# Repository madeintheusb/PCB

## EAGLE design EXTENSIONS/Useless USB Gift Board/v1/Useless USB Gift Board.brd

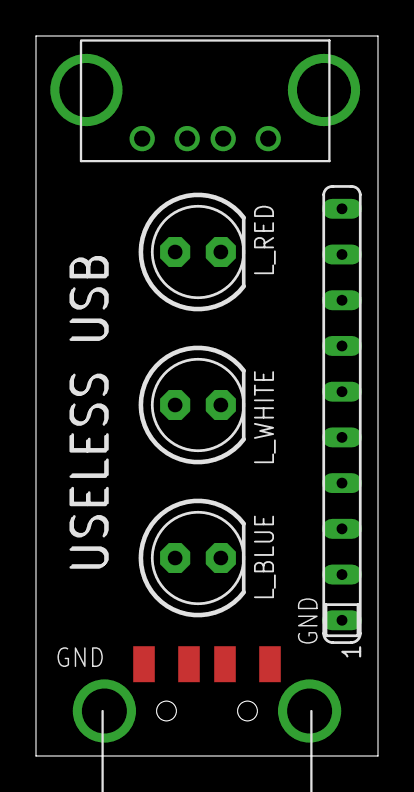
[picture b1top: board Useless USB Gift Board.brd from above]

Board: 2 copper layers, 19.0 x 40.0 mm, 6 parts (0 on the bottom side), 7 nets, no tracks yet.

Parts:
L_BLUE: LED5MM
L_RED: LED5MM
L_WHITE: LED5MM
RN1: SIP10
U$1: USB; USB-FEMALE-A-PTH
X1: USB-A; MOLEX_480371000

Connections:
unnamed: RN1.1, U$1.GND, X1.4
unnamed: L_BLUE.K, RN1.2
unnamed: U$1.D+, X1.3
unnamed: U$1.D-, X1.2
unnamed: L_RED.K, RN1.8
unnamed: L_WHITE.K, RN1.6
VCC: L_BLUE.A, L_RED.A, L_WHITE.A, U$1.VBUS, X1.1

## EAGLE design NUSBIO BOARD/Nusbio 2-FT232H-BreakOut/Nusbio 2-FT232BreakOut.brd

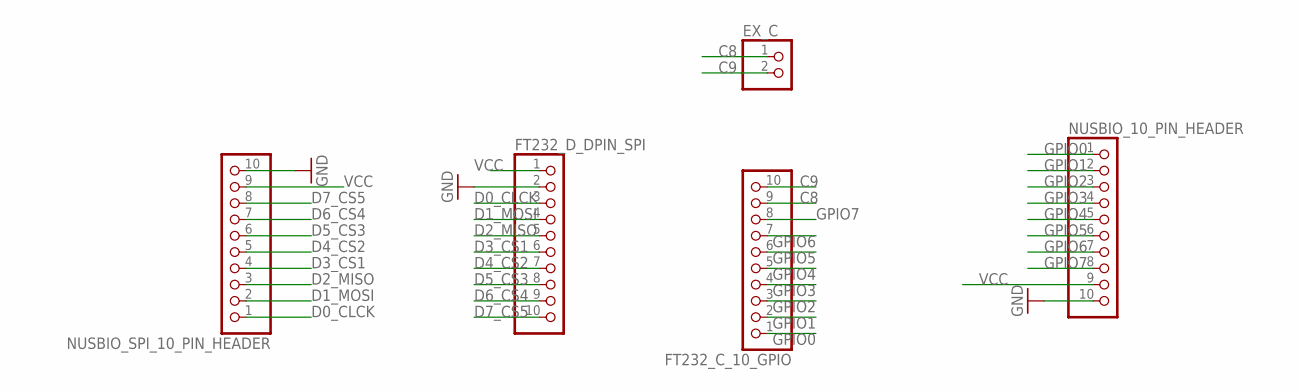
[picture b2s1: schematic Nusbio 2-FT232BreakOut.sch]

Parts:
EX_C: PINHD-1X2; 1X02
FT232_C_10_GPIO, FT232_D_DPIN_SPI: PINHD-1X10; 1X10
NUSBIO_10_PIN_HEADER: PINHD-1X10; 1X10
NUSBIO_SPI_10_PIN_HEADER: PINHD-1X10; 1X10

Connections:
C8: EX_C.1, FT232_C_10_GPIO.9
C9: EX_C.2, FT232_C_10_GPIO.10
D0_CLCK: FT232_D_DPIN_SPI.3, NUSBIO_SPI_10_PIN_HEADER.1
D1_MOSI: FT232_D_DPIN_SPI.4, NUSBIO_SPI_10_PIN_HEADER.2
D2_MISO: FT232_D_DPIN_SPI.5, NUSBIO_SPI_10_PIN_HEADER.3
D3_CS1: FT232_D_DPIN_SPI.6, NUSBIO_SPI_10_PIN_HEADER.4
D4_CS2: FT232_D_DPIN_SPI.7, NUSBIO_SPI_10_PIN_HEADER.5
D5_CS3: FT232_D_DPIN_SPI.8, NUSBIO_SPI_10_PIN_HEADER.6
D6_CS4: FT232_D_DPIN_SPI.9, NUSBIO_SPI_10_PIN_HEADER.7
D7_CS5: FT232_D_DPIN_SPI.10, NUSBIO_SPI_10_PIN_HEADER.8
GND: FT232_D_DPIN_SPI.2, NUSBIO_10_PIN_HEADER.10, NUSBIO_SPI_10_PIN_HEADER.10
GPIO0: FT232_C_10_GPIO.1, NUSBIO_10_PIN_HEADER.1
GPIO1: FT232_C_10_GPIO.2, NUSBIO_10_PIN_HEADER.2
GPIO2: FT232_C_10_GPIO.3, NUSBIO_10_PIN_HEADER.3
GPIO3: FT232_C_10_GPIO.4, NUSBIO_10_PIN_HEADER.4
GPIO4: FT232_C_10_GPIO.5, NUSBIO_10_PIN_HEADER.5
GPIO5: FT232_C_10_GPIO.6, NUSBIO_10_PIN_HEADER.6
GPIO6: FT232_C_10_GPIO.7, NUSBIO_10_PIN_HEADER.7
GPIO7: FT232_C_10_GPIO.8, NUSBIO_10_PIN_HEADER.8
VCC: FT232_D_DPIN_SPI.1, NUSBIO_10_PIN_HEADER.9, NUSBIO_SPI_10_PIN_HEADER.9

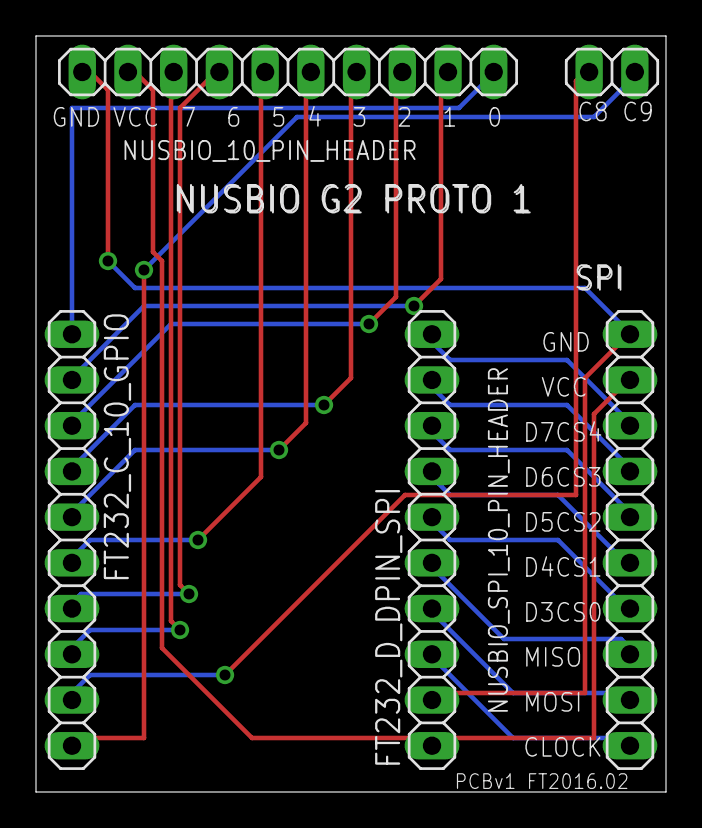
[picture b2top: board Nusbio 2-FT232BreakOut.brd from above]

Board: 2 copper layers, 35.0 x 42.0 mm, 5 parts (0 on the bottom side), 20 nets.

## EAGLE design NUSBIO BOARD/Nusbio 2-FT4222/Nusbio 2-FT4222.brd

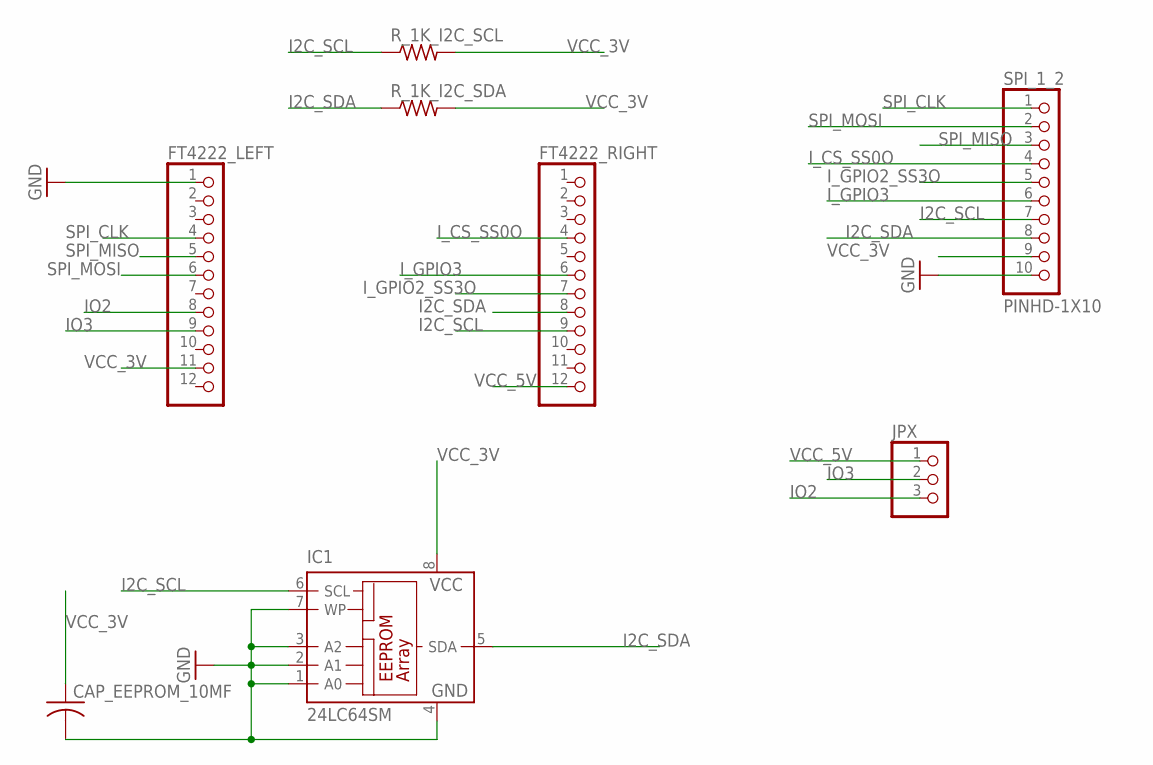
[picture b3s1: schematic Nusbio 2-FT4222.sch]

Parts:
CAP_EEPROM_10MF: C-USC1206; C1206
FT4222_LEFT, FT4222_RIGHT: PINHD-1X12; 1X12
IC1: 24LC64SM; SO-08M
JPX: PINHD-1X3; 1X03
R_1K_I2C_SCL, R_1K_I2C_SDA: R-US_R1206; R1206
SPI_1_2: PINHD-1X10; 1X10-BIG

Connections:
GND: CAP_EEPROM_10MF.2, FT4222_LEFT.1, IC1.1 (A0), IC1.2 (A1), IC1.3 (A2), IC1.4 (GND), IC1.7 (WP), SPI_1_2.10
I2C_SCL: FT4222_RIGHT.9, IC1.6 (SCL), R_1K_I2C_SCL.1, SPI_1_2.7
I2C_SDA: FT4222_RIGHT.8, IC1.5 (SDA), R_1K_I2C_SDA.1, SPI_1_2.8
IO2: FT4222_LEFT.8, JPX.3
IO3: FT4222_LEFT.9, JPX.2
I_CS_SS0O: FT4222_RIGHT.4, SPI_1_2.4
I_GPIO2_SS3O: FT4222_RIGHT.7, SPI_1_2.5
I_GPIO3: FT4222_RIGHT.6, SPI_1_2.6
SPI_CLK: FT4222_LEFT.4, SPI_1_2.1
SPI_MISO: FT4222_LEFT.5, SPI_1_2.3
SPI_MOSI: FT4222_LEFT.6, SPI_1_2.2
VCC_3V: CAP_EEPROM_10MF.1, FT4222_LEFT.11, IC1.8 (VCC), R_1K_I2C_SCL.2, R_1K_I2C_SDA.2, SPI_1_2.9
VCC_5V: FT4222_RIGHT.12, JPX.1

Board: 2 copper layers, 8 parts (4 on the bottom side), 13 nets, no tracks yet.

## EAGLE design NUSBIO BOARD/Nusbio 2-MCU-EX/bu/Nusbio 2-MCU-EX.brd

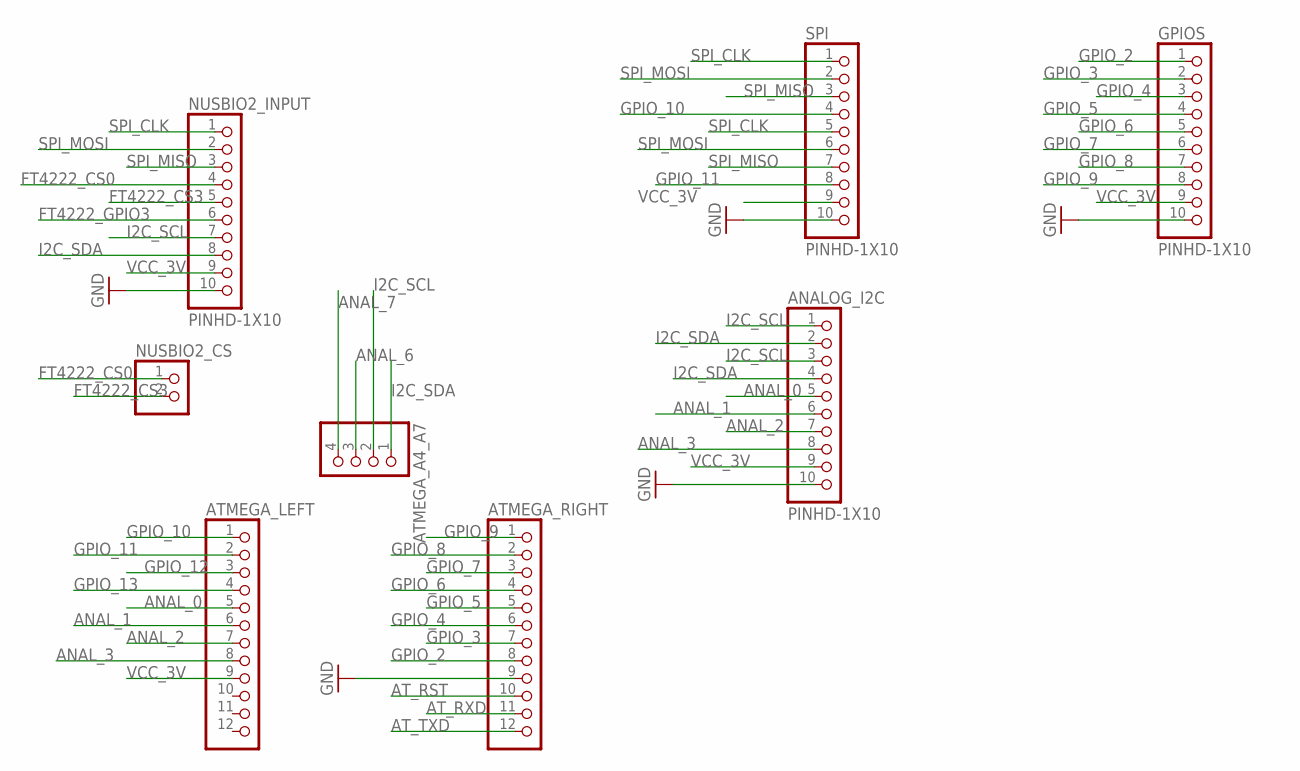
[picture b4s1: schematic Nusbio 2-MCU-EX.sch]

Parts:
ANALOG_I2C: PINHD-1X10; 1X10-BIG
ATMEGA_A4_A7: PINHD-1X4; 1X04
ATMEGA_LEFT: PINHD-1X12; 1X12
ATMEGA_RIGHT: PINHD-1X12; 1X12
GPIOS: PINHD-1X10; 1X10-BIG
NUSBIO2_CS: PINHD-1X2; 1X02
NUSBIO2_INPUT: PINHD-1X10; 1X10-BIG
SPI: PINHD-1X10; 1X10-BIG

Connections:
ANAL_0: ANALOG_I2C.5, ATMEGA_LEFT.5
ANAL_1: ANALOG_I2C.6, ATMEGA_LEFT.6
ANAL_2: ANALOG_I2C.7, ATMEGA_LEFT.7
ANAL_3: ANALOG_I2C.8, ATMEGA_LEFT.8
ANAL_6: ATMEGA_A4_A7.3
ANAL_7: ATMEGA_A4_A7.4
AT_RST: ATMEGA_RIGHT.10
AT_RXD: ATMEGA_RIGHT.11
AT_TXD: ATMEGA_RIGHT.12
FT4222_CS0: NUSBIO2_CS.1, NUSBIO2_INPUT.4
FT4222_CS3: NUSBIO2_CS.2, NUSBIO2_INPUT.5
FT4222_GPIO3: NUSBIO2_INPUT.6
GND: ANALOG_I2C.10, ATMEGA_RIGHT.9, GPIOS.10, NUSBIO2_INPUT.10, SPI.10
GPIO_2: ATMEGA_RIGHT.8, GPIOS.1
GPIO_3: ATMEGA_RIGHT.7, GPIOS.2
GPIO_4: ATMEGA_RIGHT.6, GPIOS.3
GPIO_5: ATMEGA_RIGHT.5, GPIOS.4
GPIO_6: ATMEGA_RIGHT.4, GPIOS.5
GPIO_7: ATMEGA_RIGHT.3, GPIOS.6
GPIO_8: ATMEGA_RIGHT.2, GPIOS.7
GPIO_9: ATMEGA_RIGHT.1, GPIOS.8
GPIO_10: ATMEGA_LEFT.1, SPI.4
GPIO_11: ATMEGA_LEFT.2, SPI.8
GPIO_12: ATMEGA_LEFT.3
GPIO_13: ATMEGA_LEFT.4
I2C_SCL: ANALOG_I2C.1, ANALOG_I2C.3, ATMEGA_A4_A7.2, NUSBIO2_INPUT.7
I2C_SDA: ANALOG_I2C.2, ANALOG_I2C.4, ATMEGA_A4_A7.1, NUSBIO2_INPUT.8
SPI_CLK: NUSBIO2_INPUT.1, SPI.1, SPI.5
SPI_MISO: NUSBIO2_INPUT.3, SPI.3, SPI.7
SPI_MOSI: NUSBIO2_INPUT.2, SPI.2, SPI.6
VCC_3V: ANALOG_I2C.9, ATMEGA_LEFT.9, GPIOS.9, NUSBIO2_INPUT.9, SPI.9

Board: 2 copper layers, 8 parts (0 on the bottom side), 23 nets, no tracks yet.

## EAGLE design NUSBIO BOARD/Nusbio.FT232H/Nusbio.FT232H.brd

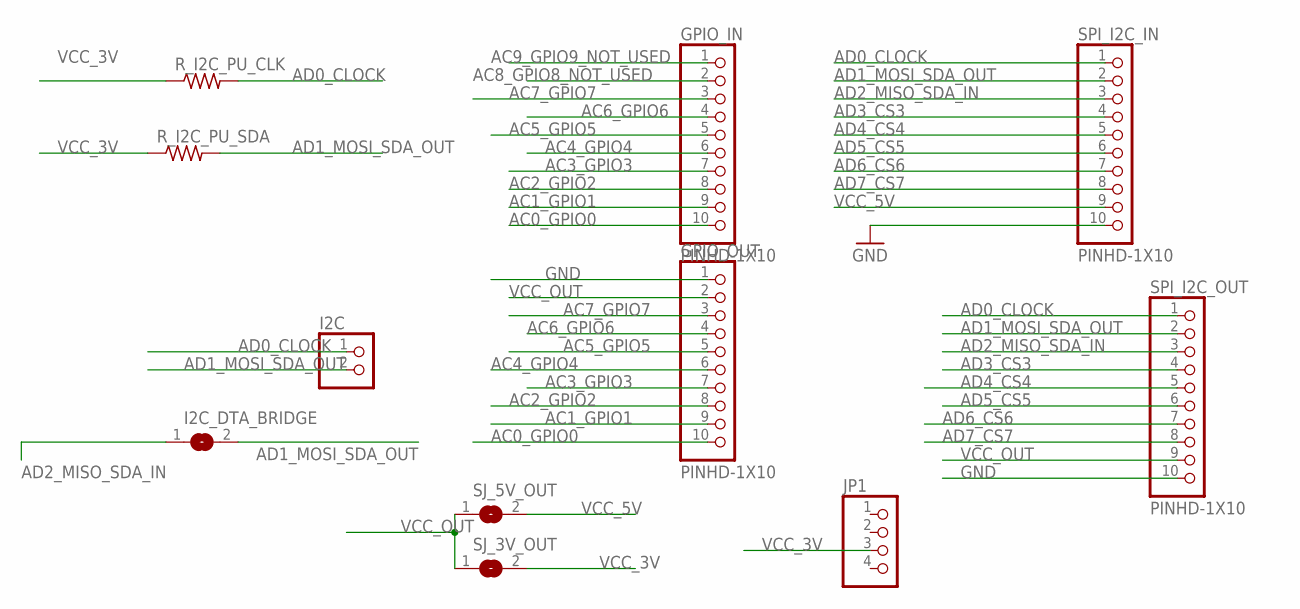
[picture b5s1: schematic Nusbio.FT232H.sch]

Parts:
GPIO_IN: PINHD-1X10; 1X10-BIG
GPIO_OUT: PINHD-1X10; 1X10-BIG
I2C: PINHD-1X2; 1X02
I2C_DTA_BRIDGE: SOLDERJUMPERREFLOW; SOLDERJUMPER_REFLOW
JP1: PINHD-1X4; 1X04
R_I2C_PU_CLK, R_I2C_PU_SDA: R-US_R1206; R1206
SJ_3V_OUT, SJ_5V_OUT: SOLDERJUMPERREFLOW; SOLDERJUMPER_REFLOW
SPI_I2C_IN, SPI_I2C_OUT: PINHD-1X10; 1X10-BIG

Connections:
AC0_GPIO0: GPIO_IN.10, GPIO_OUT.10
AC1_GPIO1: GPIO_IN.9, GPIO_OUT.9
AC2_GPIO2: GPIO_IN.8, GPIO_OUT.8
AC3_GPIO3: GPIO_IN.7, GPIO_OUT.7
AC4_GPIO4: GPIO_IN.6, GPIO_OUT.6
AC5_GPIO5: GPIO_IN.5, GPIO_OUT.5
AC6_GPIO6: GPIO_IN.4, GPIO_OUT.4
AC7_GPIO7: GPIO_IN.3, GPIO_OUT.3
AC8_GPIO8_NOT_USED: GPIO_IN.2
AC9_GPIO9_NOT_USED: GPIO_IN.1
AD0_CLOCK: I2C.1, R_I2C_PU_CLK.2, SPI_I2C_IN.1, SPI_I2C_OUT.1
AD1_MOSI_SDA_OUT: I2C.2, I2C_DTA_BRIDGE.2, R_I2C_PU_SDA.2, SPI_I2C_IN.2, SPI_I2C_OUT.2
AD2_MISO_SDA_IN: I2C_DTA_BRIDGE.1, SPI_I2C_IN.3, SPI_I2C_OUT.3
AD3_CS3: SPI_I2C_IN.4, SPI_I2C_OUT.4
AD4_CS4: SPI_I2C_IN.5, SPI_I2C_OUT.5
AD5_CS5: SPI_I2C_IN.6, SPI_I2C_OUT.6
AD6_CS6: SPI_I2C_IN.7, SPI_I2C_OUT.7
AD7_CS7: SPI_I2C_IN.8, SPI_I2C_OUT.8
GND: GPIO_OUT.1, SPI_I2C_IN.10, SPI_I2C_OUT.10
VCC_3V: JP1.3, R_I2C_PU_CLK.1, R_I2C_PU_SDA.1, SJ_3V_OUT.2
VCC_5V: SJ_5V_OUT.2, SPI_I2C_IN.9
VCC_OUT: GPIO_OUT.2, SJ_3V_OUT.1, SJ_5V_OUT.1, SPI_I2C_OUT.9

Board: 2 copper layers, 11 parts (0 on the bottom side), 20 nets, no tracks yet.

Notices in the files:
parts and their libraries:
microbuilder: This work is placed in the public domain, and may be freely used for commercial and non-commercial work with the following conditions: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
